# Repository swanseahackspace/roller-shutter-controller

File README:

# Table of Contents

- [Introduction](https://github.com/swanseahackspace/roller-shutter-controller/#introduction)
- [Hardware](https://github.com/swanseahackspace/roller-shutter-controller/#hardware)
- [Software](https://github.com/swanseahackspace/roller-shutter-controller/#software)
	- [Requirements](https://github.com/swanseahackspace/roller-shutter-controller/#requirements)
	- [Installation](https://github.com/swanseahackspace/roller-shutter-controller/#installation)
  
# Introduction
Roller Shutter RFID Access Control PCB. Uses an ESP-32-C3 (Lolin C3 Mini)

# Hardware

#### KiCad Renders

#### Assembly Render

# Software

### Requirements
- Arduino IDE or equivalent
- Arduino Libraries:
  - Adafruit Graphics
  - Adafruit SSD1306 Wemos Mini OLED

### Installation

1. Clone git repo
```
git clone https://github.com/swanseahackspace/roller-shutter-controller
```

2. Open .ino file in [Arduino IDE](https://www.arduino.cc/en/software)

3. Follow the [Wemos/Lolin C3 Mini Arduino development guide](https://www.wemos.cc/en/latest/tutorials/c3/get_started_with_arduino_c3.html)

4. Plug the board into your machine via the USB type-C port on the ESP-32-C3

5. Check the correct port is set in the Arduino IDE (Tools -> Port)

6. Upload the code to the ESP32

### Troubleshooting

*Errors uploading code to ESP-32-C3*
Use the following procedure:

- Hold on Button 9
- Press Button Reset
- Release Button 9 When you hear the prompt tone on usb reconnection

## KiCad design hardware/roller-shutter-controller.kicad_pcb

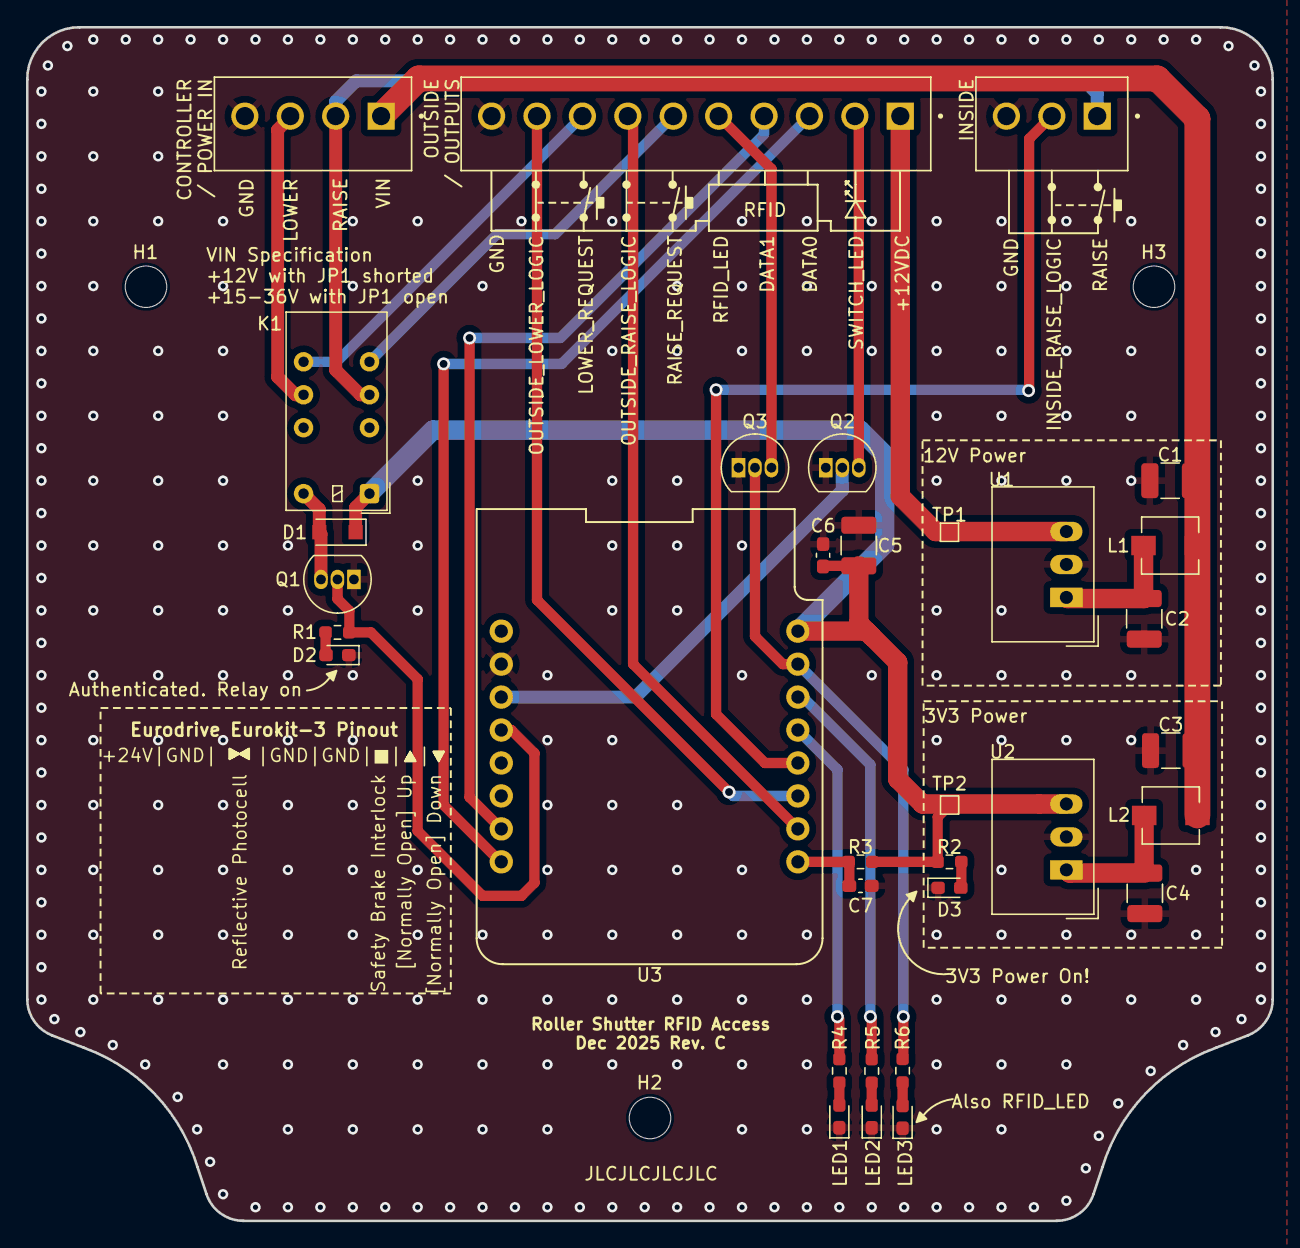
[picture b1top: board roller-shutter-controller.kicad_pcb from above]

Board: 2 copper layers, 96.0 x 92.0 mm, 36 parts (0 on the bottom side), 29 nets.

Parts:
C1, C2, C3, C4, C5: 10uF; C_1210_3225Metric_Pad1.33x2.70mm_HandSolder
C6: 0.1uF; C_0603_1608Metric_Pad1.08x0.95mm_HandSolder
C7: 1uF; C_0603_1608Metric_Pad1.08x0.95mm_HandSolder
D1: 1N4007; D_SOD-123F
D2, D3: LED; LED_0603_1608Metric_Pad1.05x0.95mm_HandSolder
H1, H2, H3: MountingHole; MountingHole_3.2mm_M3
J1: Screw_Terminal_01x06; CUI_TBP03R2-350-04BE
J2: Screw_Terminal_01x04; CUI_TBP03R2-350-03BE
J3: Screw_Terminal_01x10; CUI_TBP03R2-350-10BE
K1: EC2-3NU; Relay_DPDT_Kemet_EC2
L1, L2: 5.6uH; L_TracoPower_TCK-141
LED1, LED2, LED3: LED; LED_0603_1608Metric_Pad1.05x0.95mm_HandSolder
Q1, Q2, Q3: 2N7000; TO-92_Inline
R1, R2, R4, R5, R6: 220R; R_0603_1608Metric_Pad0.98x0.95mm_HandSolder
R3: 10k; R_0603_1608Metric_Pad0.98x0.95mm_HandSolder
TP1, TP2: TestPoint; TestPoint_Pad_1.0x1.0mm
U1: TSR_1-24120; Converter_DCDC_TRACO_TSR-1_THT
U2: TSR_1-2433; Converter_DCDC_TRACO_TSR-1_THT
U3: WeMos_C3_mini; wemos-d1-mini-with-pin-header-and-connector

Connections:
+3V3: C5.1, C6.1, D1.1 (K), K1.1, R2.2, R3.1, TP2.1, U2.3 (Vout), U3.8 (3V3)
+12V: J3.1, TP1.1, U1.3 (Vout)
+24V: C1.1, C3.1, J1.1, L1.1, L2.1
/AUTH_LED: Q2.2 (G), U3.11 (6)
/DATA0: J3.3, U3.16 (21)
/DATA1: J3.4, U3.15 (20)
/EN: C7.2, R3.2, U3.1 (EN)
/ENABLE_RELAY: Q1.2 (G), R1.2, U3.12 (7)
/INSIDE_RAISE_LOGIC: J2.2, U3.4 (1)
/LED1: R4.2, U3.5 (0)
/LED2: R5.2, U3.6 (4)
/LED3: Q3.2 (G), R6.2, U3.7 (5)
/LOWER: J1.3, K1.9
/LOWER_REQUEST: J3.8, K1.8
/OUTSIDE_LOWER_LOGIC: J3.9, U3.3 (2)
/OUTSIDE_RAISE_LOGIC: J3.7, U3.2 (3)
/RAISE: J1.2, J2.1, K1.4
/RAISE_REQUEST: J3.6, K1.5
/RFID_LED: J3.5, Q3.3 (D)
/SWITCH_LED: J3.2, Q2.3 (D)
GND: C1.2, C2.2, C3.2, C4.2, C5.2, C6.2, C7.1, D2.1 (K), D3.1 (K), J1.4, J2.3, J3.10, LED1.1 (K), LED2.1 (K), LED3.1 (K), Q1.1 (S), Q2.1 (S), Q3.1 (S), U1.2 (GND), U2.2 (GND), U3.10 (GND)
unnamed: D1.2 (A), K1.12, Q1.3 (D)
unnamed: D2.2 (A), R1.1
unnamed: D3.2 (A), R2.1
unnamed: LED1.2 (A), R4.1
unnamed: LED2.2 (A), R5.1
unnamed: LED3.2 (A), R6.1
unnamed: C2.1, L1.2, U1.1 (Vin)
unnamed: C4.1, L2.2, U2.1 (Vin)

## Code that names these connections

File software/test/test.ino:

/* Roller Shutter Controller - Test Software
  - WHAT IT DOES
   Checks the hardware is working correctly for easier debugging.
   Once the startup sequence has completed, the current uptime is shown on the screen.
   In this screen, press the button on the ESP32 module (pin 9) to toggle the relay on or off
*/

/*-----( Import needed libraries )-----*/
#include <SPI.h>
#include <Wire.h>
#include <Adafruit_GFX.h>
#include <Adafruit_SSD1306.h>

/*-----( Declare Constants and Pin Numbers )-----*/
const int brightnessLED = 20; //LED PWM Value up to 255
const long debounceDelay = 500;    // the debounce time; increase if the output flickers

#define LED1 0
#define LED2 4
#define LED3 5
#define authLED 6
#define enableRelay 7
#define data0 21
#define data1 20
#define insideRaiseLogic 1
#define outsideRaiseLogic 3
#define outsideLowerLogic 2
#define button 9

static const unsigned char PROGMEM logo_bmp[] =
{ 0xff, 0xff, 0xff, 0xff, 0xff, 0xff, 0xff, 0xff, 0xe0, 0x07, 0xff, 0xff, 0xff, 0xfe, 0x00, 0x00,
  0x7f, 0xff, 0xff, 0xf8, 0x05, 0xa0, 0x1f, 0xff, 0xff, 0xf0, 0x7f, 0xfe, 0x0f, 0xff, 0xff, 0xc1,
  0xff, 0xff, 0x83, 0xff, 0xff, 0x87, 0xfe, 0x7f, 0xe1, 0xff, 0xff, 0x0f, 0xfc, 0x3f, 0xf0, 0xff,
  0xfe, 0x3f, 0xf8, 0x1f, 0xfc, 0x7f, 0xfc, 0x7f, 0xf0, 0x0f, 0xfe, 0x3f, 0xf8, 0xff, 0xe0, 0x07,
  0xfe, 0x1f, 0xf8, 0xff, 0xc0, 0x07, 0xff, 0x1f, 0xf1, 0xff, 0x80, 0x07, 0xff, 0x8f, 0xe3, 0xff,
  0x00, 0x03, 0xff, 0xc7, 0xe3, 0xff, 0x00, 0x01, 0xff, 0xc7, 0xc7, 0xfd, 0x80, 0x00, 0xff, 0xe7,
  0xc7, 0xf9, 0x80, 0x00, 0x7f, 0xe3, 0xcf, 0xf0, 0xe0, 0x00, 0x3f, 0xe3, 0xcf, 0xe0, 0x30, 0x00,
  0x17, 0xf1, 0x8f, 0xc0, 0x1f, 0x00, 0x03, 0xf1, 0x8f, 0x80, 0x1e, 0x00, 0x01, 0xf1, 0x9f, 0x00,
  0x0c, 0x00, 0x00, 0xf1, 0x8e, 0x00, 0x18, 0x00, 0x00, 0x79, 0x9c, 0x00, 0x10, 0x00, 0x00, 0x31,
  0x80, 0x00, 0x00, 0x00, 0x00, 0x01, 0x88, 0x00, 0x00, 0x00, 0x00, 0x51, 0x82, 0x00, 0x00, 0x00,
  0x00, 0x01, 0x82, 0x00, 0x00, 0x10, 0x00, 0xa1, 0x84, 0x40, 0x00, 0x10, 0x00, 0x81, 0x85, 0x00,
  0x00, 0x00, 0x02, 0x23, 0xc0, 0x50, 0x00, 0x02, 0x00, 0xa3, 0xc5, 0x08, 0x00, 0x00, 0x0a, 0x03,
  0xc0, 0x52, 0x00, 0x00, 0x88, 0xa3, 0xe1, 0x12, 0x00, 0x00, 0x4a, 0x07, 0xe1, 0x24, 0x40, 0x00,
  0x10, 0x87, 0xf0, 0x91, 0x00, 0x01, 0x4a, 0x0f, 0xf8, 0x25, 0x00, 0x00, 0x10, 0x0f, 0xf8, 0x21,
  0x40, 0x05, 0x4a, 0x1f, 0xfc, 0x0a, 0x10, 0x00, 0x10, 0x3f, 0xfe, 0x02, 0x80, 0x15, 0x48, 0x7f,
  0xff, 0x08, 0x54, 0x01, 0x10, 0xff, 0xff, 0x85, 0x00, 0x54, 0x81, 0xff, 0xff, 0xc0, 0x55, 0x01,
  0x03, 0xff, 0xff, 0xe0, 0x10, 0xa8, 0x07, 0xff, 0xff, 0xf8, 0x01, 0x00, 0x1f, 0xff, 0xff, 0xfe,
  0x00, 0x00, 0x7f, 0xff, 0xff, 0xff, 0xc0, 0x07, 0xff, 0xff, 0xff, 0xff, 0xff, 0xff, 0xff, 0xff
};

/*-----( Declare objects )-----*/
//Initialise display library with no reset pin by passing it -1
Adafruit_SSD1306 display(-1);

#if (SSD1306_LCDHEIGHT != 48)
#error("Height incorrect, please fix Adafruit_SSD1306.h!");
#endif

/*-----( Declare Variables )-----*/
int buttonState = 0; // state of on-module button
int relayState = 0;

long lastDebounceTime = 0;  // the last time the output pin was toggled


void setup() { /****** SETUP: RUNS ONCE ******/

  //setup GPIO
  pinMode(LED1, OUTPUT);
  pinMode(LED2, OUTPUT);
  pinMode(LED3, OUTPUT);
  pinMode(enableRelay, OUTPUT);
  pinMode(button, INPUT_PULLUP);

  Serial.begin(9600);

  // generate display voltage from 3V3 rail
  display.begin(SSD1306_SWITCHCAPVCC, 0x3C);  // initialize with the I2C addr 0x3C (for the 64x48)

  display.setRotation(2);
  display.clearDisplay();
  // display init complete

  display.drawBitmap(8, 0, logo_bmp, 48, 48, 1);
  display.display();
  delay(1000);

  display.setTextSize(1);
  display.setTextColor(WHITE);

  testHardware();


} //--(end setup )---

void loop() { /****** LOOP: RUNS CONSTANTLY ******/

  buttonState = !digitalRead(button);

  //filter out any noise by setting a time buffer
  if ( (millis() - lastDebounceTime) > debounceDelay) {

    //if the button has been pressed, lets toggle the LED from "off to on" or "on to off"
    if ( (buttonState == HIGH) && (relayState == 0) ) {

      digitalWrite(enableRelay, HIGH);
      relayState = 1;
      lastDebounceTime = millis();
    }
    else if ( (buttonState == HIGH) && (relayState == 1) ) {

      digitalWrite(enableRelay, LOW);
      relayState = 0;
      lastDebounceTime = millis();
    }
  }

  display.clearDisplay();
  display.setCursor(0, 0);
  display.println("*Uptime*");
  display.println("");
  display.print("Relay: ");
  display.println(relayState);
  display.print(uptime());
  display.display();

} //--(end main loop )---

/*-----( Declare User-written Functions )-----*/
void testHardware() {
  display.clearDisplay();
  display.setCursor(0, 0);
  display.println("*Testing*");

  display.print("LED1");
  display.display();
  testLED(LED1);
  display.print("LED2");
  display.display();
  testLED(LED2);
  display.print("LED3");
  display.display();
  testLED(LED3);

  delay(500);

  testRelay();

  delay(500);

}

void testLED(int pinNumber) {
  analogWrite(pinNumber, brightnessLED);
  for (int i = 0; i < 3; i++) {
    display.print(".");
    display.display();
    delay(300);
  }
  display.println("OK");
  display.display();
  analogWrite(pinNumber, 0);
  delay(200);
}

void testRelay() {
  display.clearDisplay();
  display.setCursor(0, 0);
  display.println("*Relay*");
  display.println("");
  display.print("On");
  display.display();

  digitalWrite(enableRelay, HIGH);
  for (int i = 0; i < 4; i++) {
    display.print(".");
    display.display();
    delay(300);
  }
  display.println("OK");
  display.display();
  delay(200);

  display.print("Off");

  digitalWrite(enableRelay, LOW);
  for (int i = 0; i < 3; i++) {
    display.print(".");
    display.display();
    delay(300);
  }
  display.println("OK");
  display.display();
  delay(200);
}

char *uptime() // Function made to millis() be an optional parameter
{
  return (char *)uptime(millis()); // call original uptime function with unsigned long millis() value
}

char *uptime(unsigned long milli)
{
  static char _return[32];
  unsigned long secs = milli / 1000, mins = secs / 60;
  unsigned int hours = mins / 60, days = hours / 24;
  milli -= secs * 1000;
  secs -= mins * 60;
  mins -= hours * 60;
  hours -= days * 24;
  sprintf(_return, "%2.2d days   %2.2d:%2.2d:%2.2d", (byte)days, (byte)hours, (byte)mins, (byte)secs, (int)milli);
  return _return;
}

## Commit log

2023-03-07 added hardware
2023-03-07 Create LICENCE
2023-03-07 Rename README to README.md
2023-03-07 Added more detail about the enclosure
2023-03-07 test software for hardware debugging
2023-03-07 added existing codebase as submodule
2023-03-07 Added submodule info
2023-06-20 updated submodule to forked doorlock repo
2023-06-20 changed software branch to dev version
2023-06-20 updated submodule
2025-11-29 started work on new rev
2025-11-29 started new rev
2025-11-29 first draft of v4 schematic
2025-12-06 forgot to git add everything..
2026-01-23 swapped DC-DCs, upgraded to S3
2026-01-25 schematic WIP
2026-01-25 git things
